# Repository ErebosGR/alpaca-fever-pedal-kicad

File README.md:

View this project on [CADLAB.io](https://cadlab.io/project/25413). 

# Alpaca Fever pedal KiCad project
 This is the KiCad project for the Alpaca Fever, an overdrive guitar pedal based on the Way Huge Red Llama with an added Big Muff-style Tone control.

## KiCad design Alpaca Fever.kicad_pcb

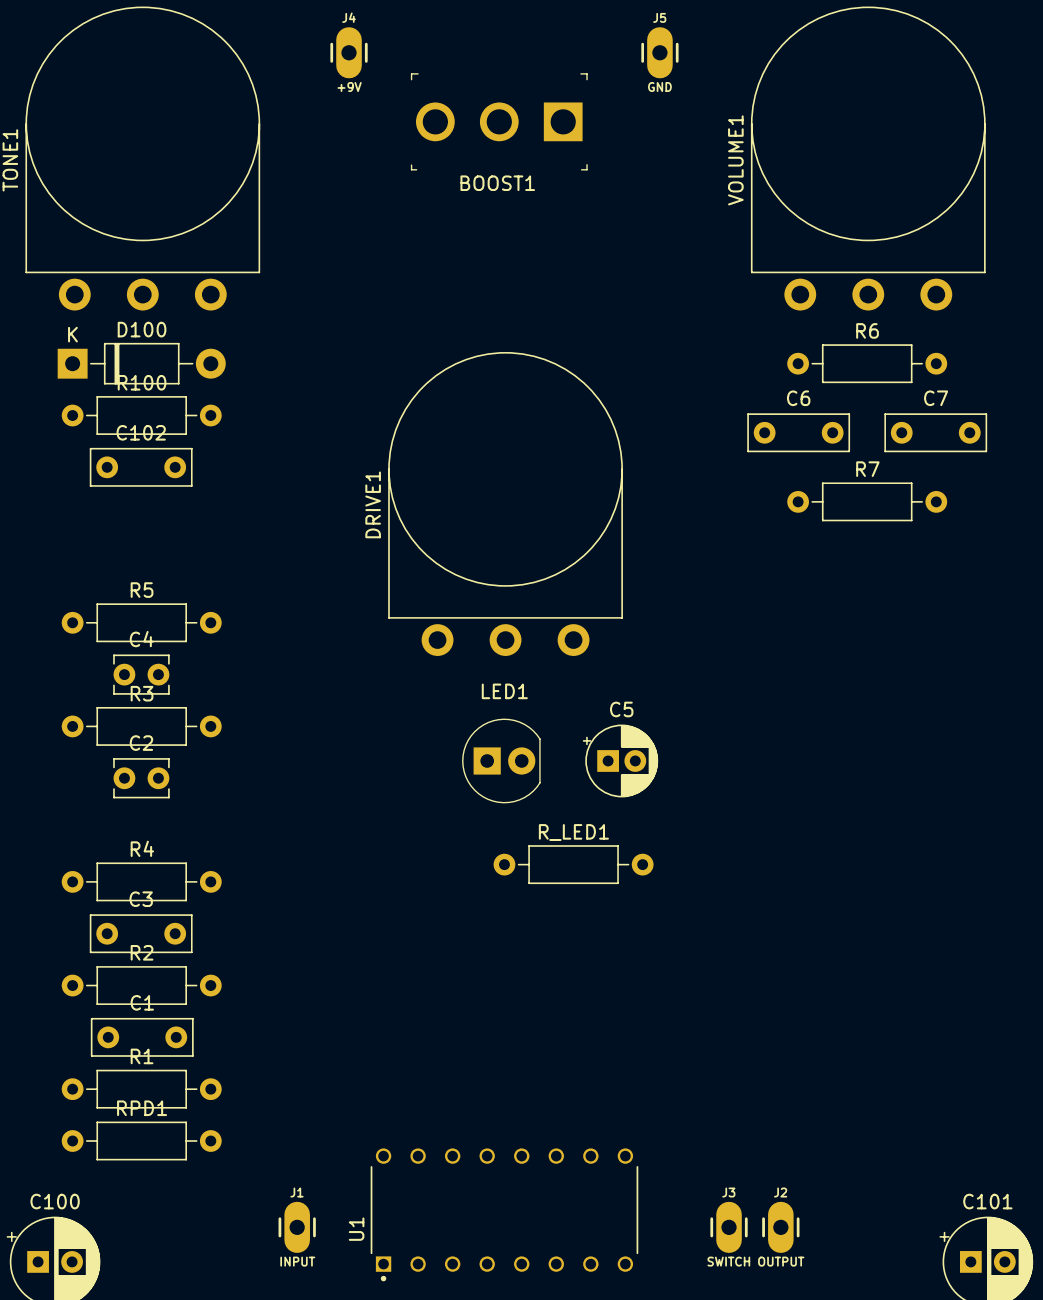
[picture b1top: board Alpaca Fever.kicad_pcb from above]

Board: 2 copper layers, 32 parts (0 on the bottom side), 19 nets, no tracks yet.

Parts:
BOOST1: on-off-on; Toggle_Switch_100SP1T1B4M2QE
C1: 68nF; C_Rect_L7.2mm_W2.5mm_P5.00mm_FKS2_FKP2_MKS2_MKP2
C2: 47pF; C_Disc_D3.8mm_W2.6mm_P2.50mm
C3: 33nF; C_Rect_L7.2mm_W2.5mm_P5.00mm_FKS2_FKP2_MKS2_MKP2
C4: 100pF; C_Disc_D3.8mm_W2.6mm_P2.50mm
C5: 10uF; CP_Radial_D5.0mm_P2.00mm
C6, C7: 22nF; C_Rect_L7.2mm_W2.5mm_P5.00mm_FKS2_FKP2_MKS2_MKP2
C100, C101: 220uF; CP_Radial_D6.3mm_P2.50mm
C102: 100nF; C_Rect_L7.2mm_W2.5mm_P5.00mm_FKS2_FKP2_MKS2_MKP2
D100: 1N5817; D_DO-41_SOD81_P10.16mm_Horizontal
DRIVE1: B1M; Potentiometer_Omeg_PC16BU_Vertical
J1: INPUT; 1X01_LONGPAD
J2: OUTPUT; 1X01_LONGPAD
J3: SWITCH; 1X01_LONGPAD
J4: +9V; 1X01_LONGPAD
J5: GND; 1X01_LONGPAD
LED1: RED; LED_5mm_Radial
R1, R4: 100k; R_Axial_DIN0207_L6.3mm_D2.5mm_P10.16mm_Horizontal
R2: 6M8; R_Axial_DIN0207_L6.3mm_D2.5mm_P10.16mm_Horizontal
R3: 2M2; R_Axial_DIN0207_L6.3mm_D2.5mm_P10.16mm_Horizontal
R5: 1M; R_Axial_DIN0207_L6.3mm_D2.5mm_P10.16mm_Horizontal
R6: 10k; R_Axial_DIN0207_L6.3mm_D2.5mm_P10.16mm_Horizontal
R7: 47k; R_Axial_DIN0207_L6.3mm_D2.5mm_P10.16mm_Horizontal
R100: 1K; R_Axial_DIN0207_L6.3mm_D2.5mm_P10.16mm_Horizontal
RPD1: 1M; R_Axial_DIN0207_L6.3mm_D2.5mm_P10.16mm_Horizontal
R_LED1: 4k7; R_Axial_DIN0207_L6.3mm_D2.5mm_P10.16mm_Horizontal
TONE1: B100k; Potentiometer_Omeg_PC16BU_Vertical
U1: CD4049UBE; DIP794W45P254L1969H508Q16
VOLUME1: A10k; Potentiometer_Omeg_PC16BU_Vertical

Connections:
9: C3.2, C4.2, R5.2, U1.9
+9V: D100.2, J4.1
GND: C7.1, C100.2, C101.2, C102.2, J5.1, R7.2, RPD1.2, U1.8, VOLUME1.1
unnamed: BOOST1.1, R4.2
unnamed: BOOST1.2, DRIVE1.1, R2.1
unnamed: BOOST1.3, R3.2
unnamed: C1.1, C2.1, R2.2, R3.1, R4.1, U1.14
unnamed: C1.2, R1.2
unnamed: C2.2, C3.1, DRIVE1.2, DRIVE1.3, U1.15
unnamed: C4.1, C5.1, R5.1, U1.10
unnamed: C5.2, C6.1, R6.1
unnamed: C6.2, R7.1, TONE1.3
unnamed: C7.2, R6.2, TONE1.1
unnamed: C102.1, D100.1, R100.1
unnamed: J1.1, R1.1, RPD1.1
unnamed: J2.1, VOLUME1.2
unnamed: J3.1, R_LED1.2
unnamed: TONE1.2, VOLUME1.3
VCC: C100.1, C101.1, R100.2, U1.1, U1.3, U1.5, U1.7, U1.11

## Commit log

2022-04-12 Backlink to CADLAB.io has been added.
2022-04-15 Cleaned up some connectors and power flags
2022-04-17 Create LICENSE
